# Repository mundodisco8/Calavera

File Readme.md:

# Calavera Badge

We wanted to run a "lunch and learn" day at the company I used to work about soldering. I always liked [Protopic's Day of the Geek Soldering Badge](https://www.proto-pic.co.uk/day-of-the-geek-badge/), but it only turns two LEDs on when you slide the battery, and I thought that my mates would need a bit more than a couple of LEDs to be able to say that they know how to solder, so I thought on modifying. I checked around but it seems the project is not open source, so I decided to ~~blatantly copy~~ get inspired by them.

So here I was, thinking how to improve it, if I should go nuts or keep it simple. Danny, what should I do? should I go simple?

As I wanted to do a bit more, I decided to add two features:

* A way to turn it on and off. I thought adding a slider switch (and that would be a terrific idea in any case). I had never experimented with cap touch, so I thought in giving it a go.
* Add a "breathe" effect to the LEDs.

The schematic includes instructions on pretty much everything, so I recommend checking it. You can choose how challenging you want it to be, from "slide battery to get LEDs on" to "cap touch with breathe effect" and all the possibilities in between.

Turns out the badge is a bit overkill. It took me around 30 minutes to do one, and a colleague that has never soldered took something around 2-3h to finish it.

I was testing Cadlab when I was doing this project, you can view this project [here](https://cadlab.io/project/2044).

## Variants

I wanted to experiment with plated PCB borders. It gives it a very nice touch, but they are expensive, so you might want to make a cheaper version. There are two "footprints" for the soldermask "part", so you can choose to have the plated border or not. You might want to run the "Border" variant even without plated borders to get a nice copper outline, too. In any case, this board is yelling to be finished in ENIG, so please expend some money on that. Is not that expensive.

## The support folder

You can find the original SVG used for the art, as well as some SVGs I used to

## Known Issues / To Do:

* Tweak the cap touch pad / circuitry. Right now the cap touch feature is not very reliable. The values are the standard ones provided in the datasheet. A bit of experimenting could make it more reliable, but who has time for that, right?

## Acknowledgements

* [Terayza](https://github.com/Terayza) for her invaluable help.
* Protopic for doing their Day of the Geek soldering badge. Theirs is infinitely nicer than mine.
* The graphic on the top silkscreen / soldermask is taken from [Freepik](www.freepik.com).
* [The SVG2Shenzhen plugin.](https://github.com/badgeek/svg2shenzhen)
* My mate Danny DV, for being so nice and lending his image for this readme.

## Changelog

### v0.3.1-RC1 - 30th October 2023

* Moved the project to KiCad 7, and took the opportunity to tweak some footprints and the art.
* Made the touch area a bit bigger.

### v0.3.0 (untested, never produced) - 28th October 2022

Slightly improved version.

* Changed the double NMOS for a single one. Package is the "same" than v0.2.0 (SOT23), but having only 3 pins should make it way simpler to solder. We don't drive current, so we don't need two transistors.
* Cleaned the track layout
* Added a switch so you can fully turn it off when not in use.
* Added a couple of good practices from [ST's AN4312](https://www.st.com/resource/en/application_note/dm00087990-design-with-surface-sensors-for-touch-sensing-applications-on-mcus-stmicroelectronics.pdf). Hatched the ground below the pad and made its trace to the sensor thinner. Planes connected to ground which increases the parasitic capacitance on the cap sensor (bad) but it's better than a floating plane as it was before (worse).

### v0.2.0 (untested, never produced) - 10th January 2020

Slightly improved version.

* Cleaned the folder structure. Now all the parts are in the same library, and all the 3D models are relatively referenced to the project path.
* Changed the transistor to a SOT23. Should be easier to solder.
* Increased the track width.
* Made the border slightly thinner, I think? I don't remember. Probably.
* Isolated the ground plane from the copper pour, because I suspect that it will improve the touch response, but I have no idea if it will work.

### v0.1.0 - 23rd September 2019

First version of this board. It works 💃🎉🚀🦼! But not very well 💣🥦...

* Cap touch is hit and miss. I think that the fact that the border is exposed and tied to ground makes that when you hold it, you mess with the electric field. The whole subcircuit might need a makeover.
* The tracks are very thin and can be ripped up by a young padawan.
* The transistor footprint is devilishly difficult to solder even for an experienced Jedi.

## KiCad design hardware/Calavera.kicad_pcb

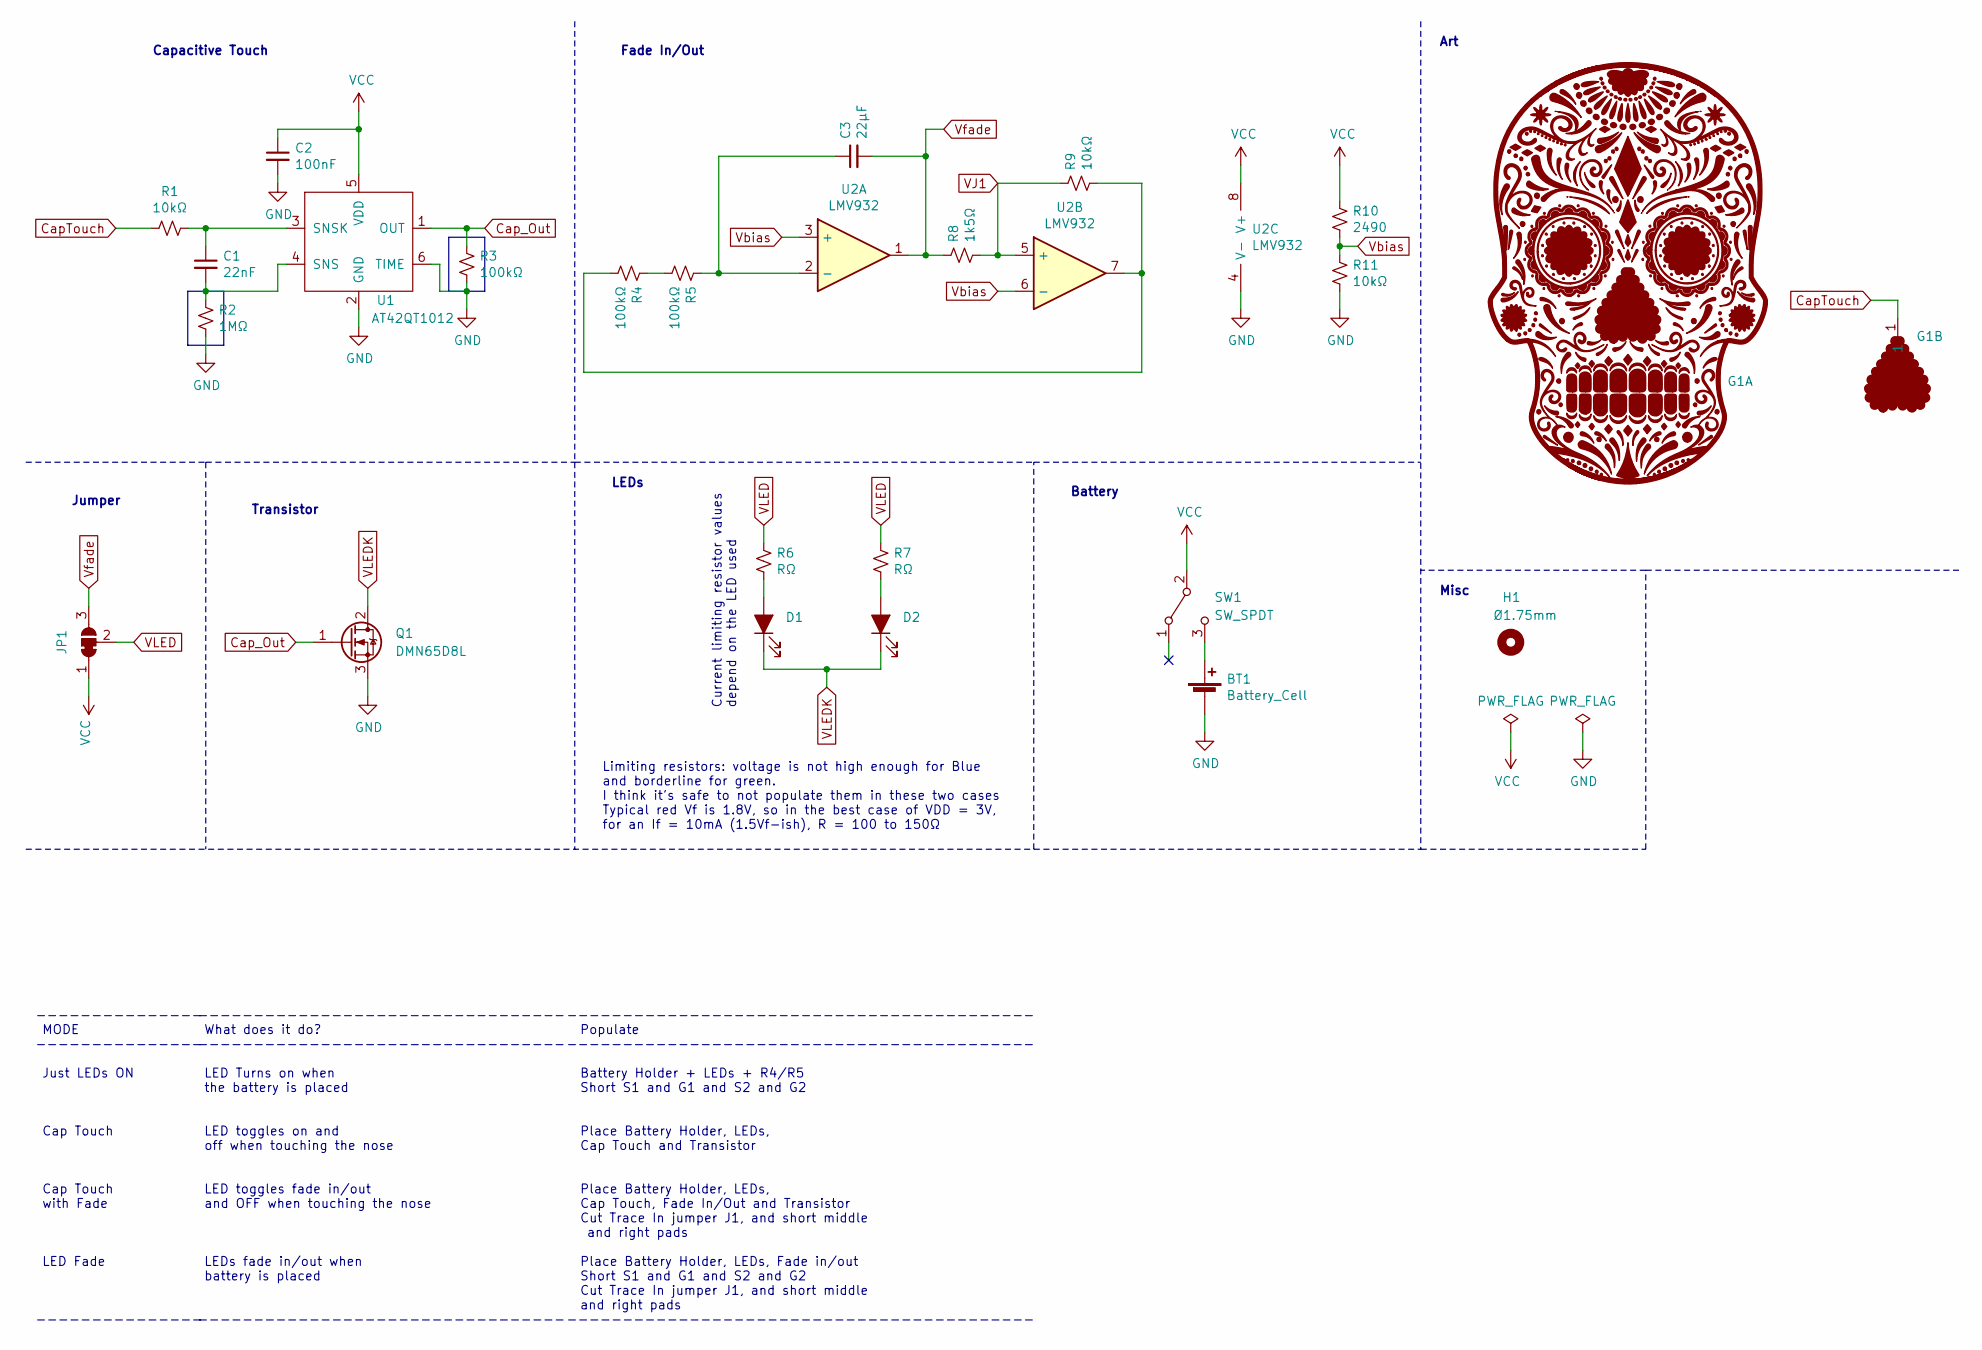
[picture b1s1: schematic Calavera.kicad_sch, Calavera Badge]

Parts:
BT1: Battery_Cell; CR2032_Keystone_3024; MPN 3034; Digikey PN 36-3034-ND
C1: 22nF; 0805-C_Handsolder; Tolerance X7R; MPN 885342207011; Digikey PN 732-12080-1-ND
C2: 100nF; 0805-C_Handsolder; Tolerance X7R; MPN CL21B104KBCNNNC; Digikey PN 1276-1003-1-ND
C3: 22μF; 0805-C_Handsolder; Tolerance X7R; MPN GRM21BZ71A226ME15L; Digikey PN 490-GRM21BZ71A226ME15LCT-ND
D1, D2: LED_Small_ALT; LED_D3.0mm_ThroughHole; MPN N/A; Digikey PN N/A
G1: Calavera_Art; MPN N/A; Digikey PN N/A
H1: Ø1.75mm; MountingHole_1.75mm; MPN N/A; Digikey PN N/A
JP1: SolderJumper_3_Bridged12; SolderJumper-3_P1.3mm_Bridged12_RoundedPad1.0x1.5mm; MPN N/A; Digikey PN N/A
Q1: DMN65D8L; SOT-23_NMOS_DMN65D8L; MPN DMN65D8L; Digikey PN DMN65D8L-7DICT-ND
R1, R9, R11: 10kΩ; 0805-R_Handsolder; Tolerance ±1%, 1/8W; MPN CR0805-FX-1002ELF; Digikey PN CR0805-FX-1002ELFCT-ND
R2: 1MΩ; 0805-R_Handsolder; Tolerance ±1%, 1/8W; MPN CR0805-FX-1004ELF; Digikey PN CR0805-FX-1004ELFCT-ND
R3, R4, R5: 100kΩ; 0805-R_Handsolder; Tolerance ±1%, 1/8W; MPN CR0805-FX-1003ELF; Digikey PN CR0805-FX-1003ELFCT-ND
R6, R7: RΩ; 0805-R_Handsolder; MPN N/A; Digikey PN N/A
R8: 1k5Ω; 0805-R_Handsolder; Tolerance ±1%, 1/8W; MPN CR0805-FX-1501ELF; Digikey PN CR0805-FX-1501ELFCT-ND
R10: 2490; 0805-R_Handsolder; Tolerance ±1%, 1/8W; MPN CR0805-FX-2491ELF; Digikey PN CR0805-FX-2491ELFCT-ND
SW1: SW_SPDT; Slider_Switch_C&K_AYZ0102AGRLC_SPDT_RightAngle; MPN AYZ0102AGRLC; Digikey PN 401-2012-1-ND
U1: AT42QT1012; SOT23-6-AT42QT1012; MPN AT42QT1012-TSHR; Digikey PN 401-2012-1-ND
U2: LMV932; SOIC-8_Dual_OpAmp_Handsolder; MPN LMV932DR2G; Digikey PN LMV932DR2GOSCT-ND

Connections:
CapTouch: G1.1, R1.2
Cap_Out: Q1.1 (G), R3.1, U1.1 (OUT)
GND: BT1.-, C2.2, Q1.3 (S), R2.2, R3.2, R11.2, U1.2 (GND), U1.6 (TIME), U2.4 (V-)
unnamed: D1.2 (A), R6.2
unnamed: D2.2 (A), R7.2
unnamed: R4.1, R5.2
unnamed: R4.2, R9.2, U2.7
unnamed: BT1.+, SW1.3 (C)
unnamed: C1.2, R2.1, U1.4 (SNS)
unnamed: C1.1, R1.1, U1.3 (SNSK)
unnamed: C3.1, R5.1, U2.2 (-)
VCC: C2.1, JP1.1 (A), R10.1, SW1.2 (B), U1.5 (VDD), U2.8 (V+)
VJ1: R8.2, R9.1, U2.5 (+)
VLED: JP1.2 (C), R6.1, R7.1
VLEDK: D1.1 (K), D2.1 (K), Q1.2 (D)
Vbias: R10.2, R11.1, U2.3 (+), U2.6 (-)
Vfade: C3.2, JP1.3 (B), R8.1, U2.1

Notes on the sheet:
Battery
--------------- MODE --------------- Just LEDs ON Cap Touch Cap Touch with Fade LED Fade ---------------
Capacitive Touch
Misc
Current limiting resistor values depend on the LED used
Jumper
Fade In/Out
Transistor
Limiting resistors: voltage is not high enough for Blue and borderline for green. I think it's safe to not populate them in these two cases Typical red Vf is 1.8V, so in the best case of VDD = 3V, for an If = 10mA (1.5Vf-ish), R = 100 to 150Ω
--------------------------------- What does it do? --------------------------------- LED Turns on when the battery is placed LED toggles on and off when touching the nose LED toggles fade in/out and OFF when touching the nose LEDs fade in/out when battery is placed ---------------------------------
------------------------------------------ Populate ------------------------------------------ Battery Holder + LEDs + R4/R5 Short S1 and G1 and S2 and G2 Place Battery Holder, LEDs, Cap Touch and Transistor Place Battery Holder, LEDs, Cap Touch, Fade In/Out and Transistor Cut Trace In jumper J1, a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
LEDs
Art

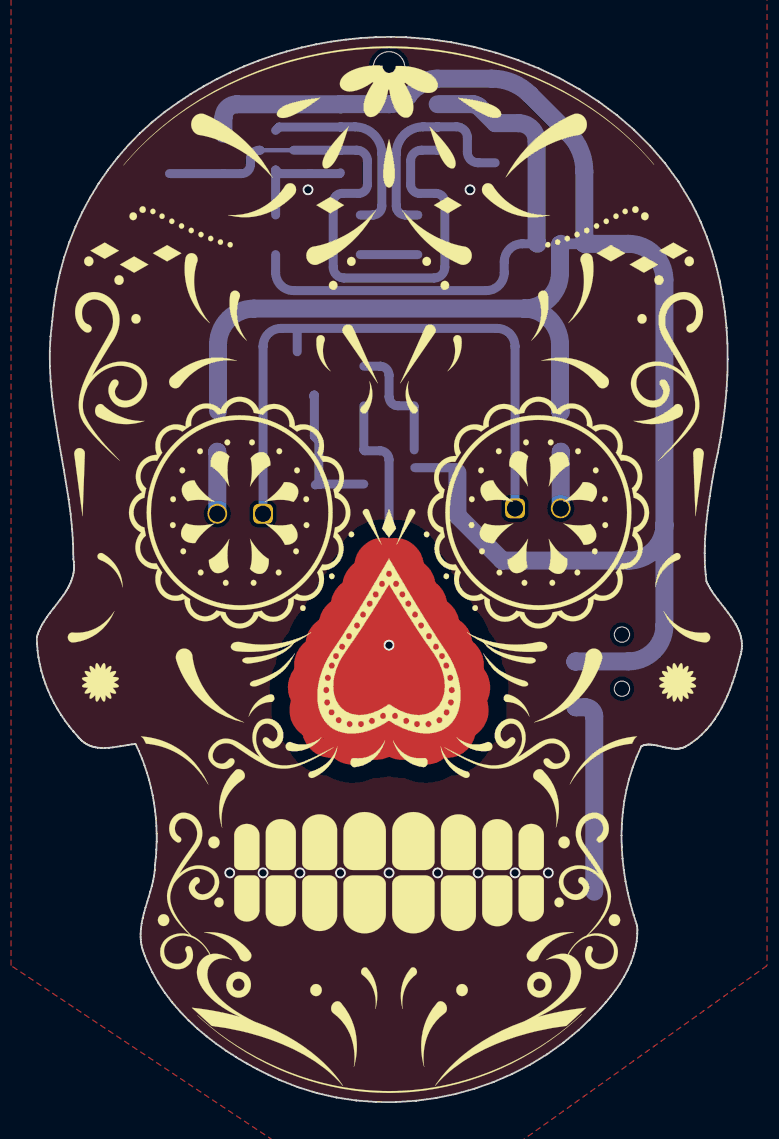
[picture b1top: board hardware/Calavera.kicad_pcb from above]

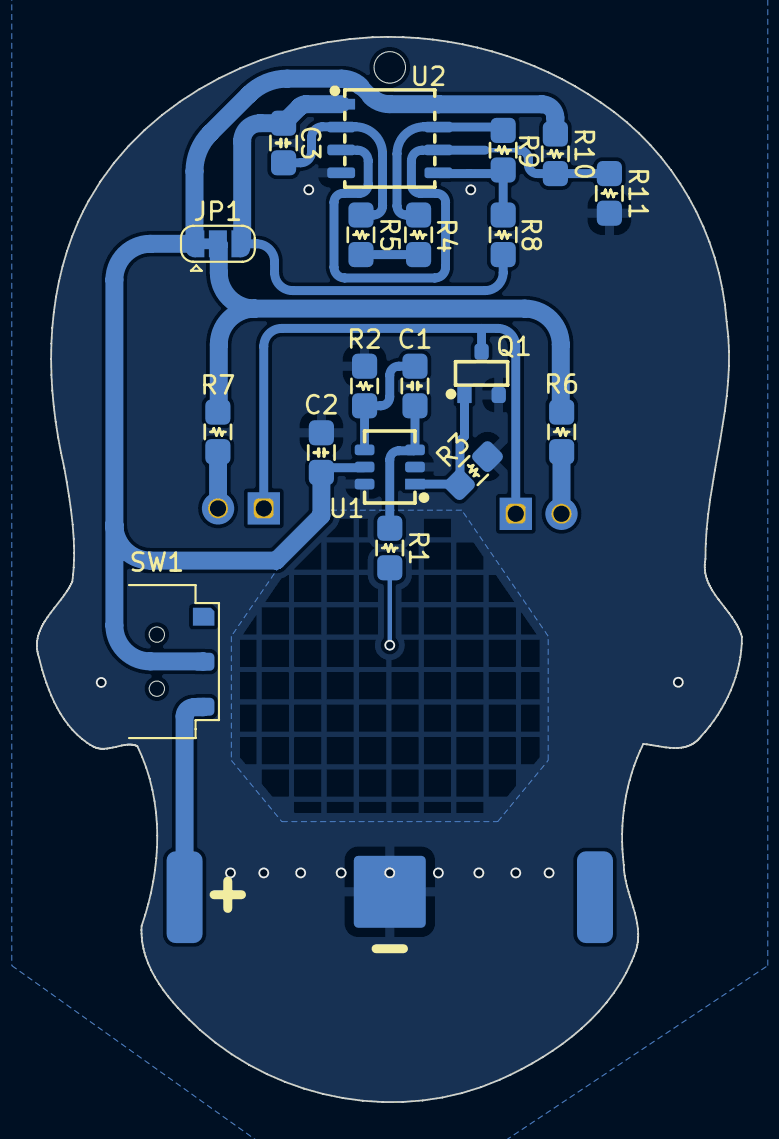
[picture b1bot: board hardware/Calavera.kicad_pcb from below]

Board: 2 copper layers, 39.2 x 59.2 mm, 24 parts (20 on the bottom side), 17 nets.

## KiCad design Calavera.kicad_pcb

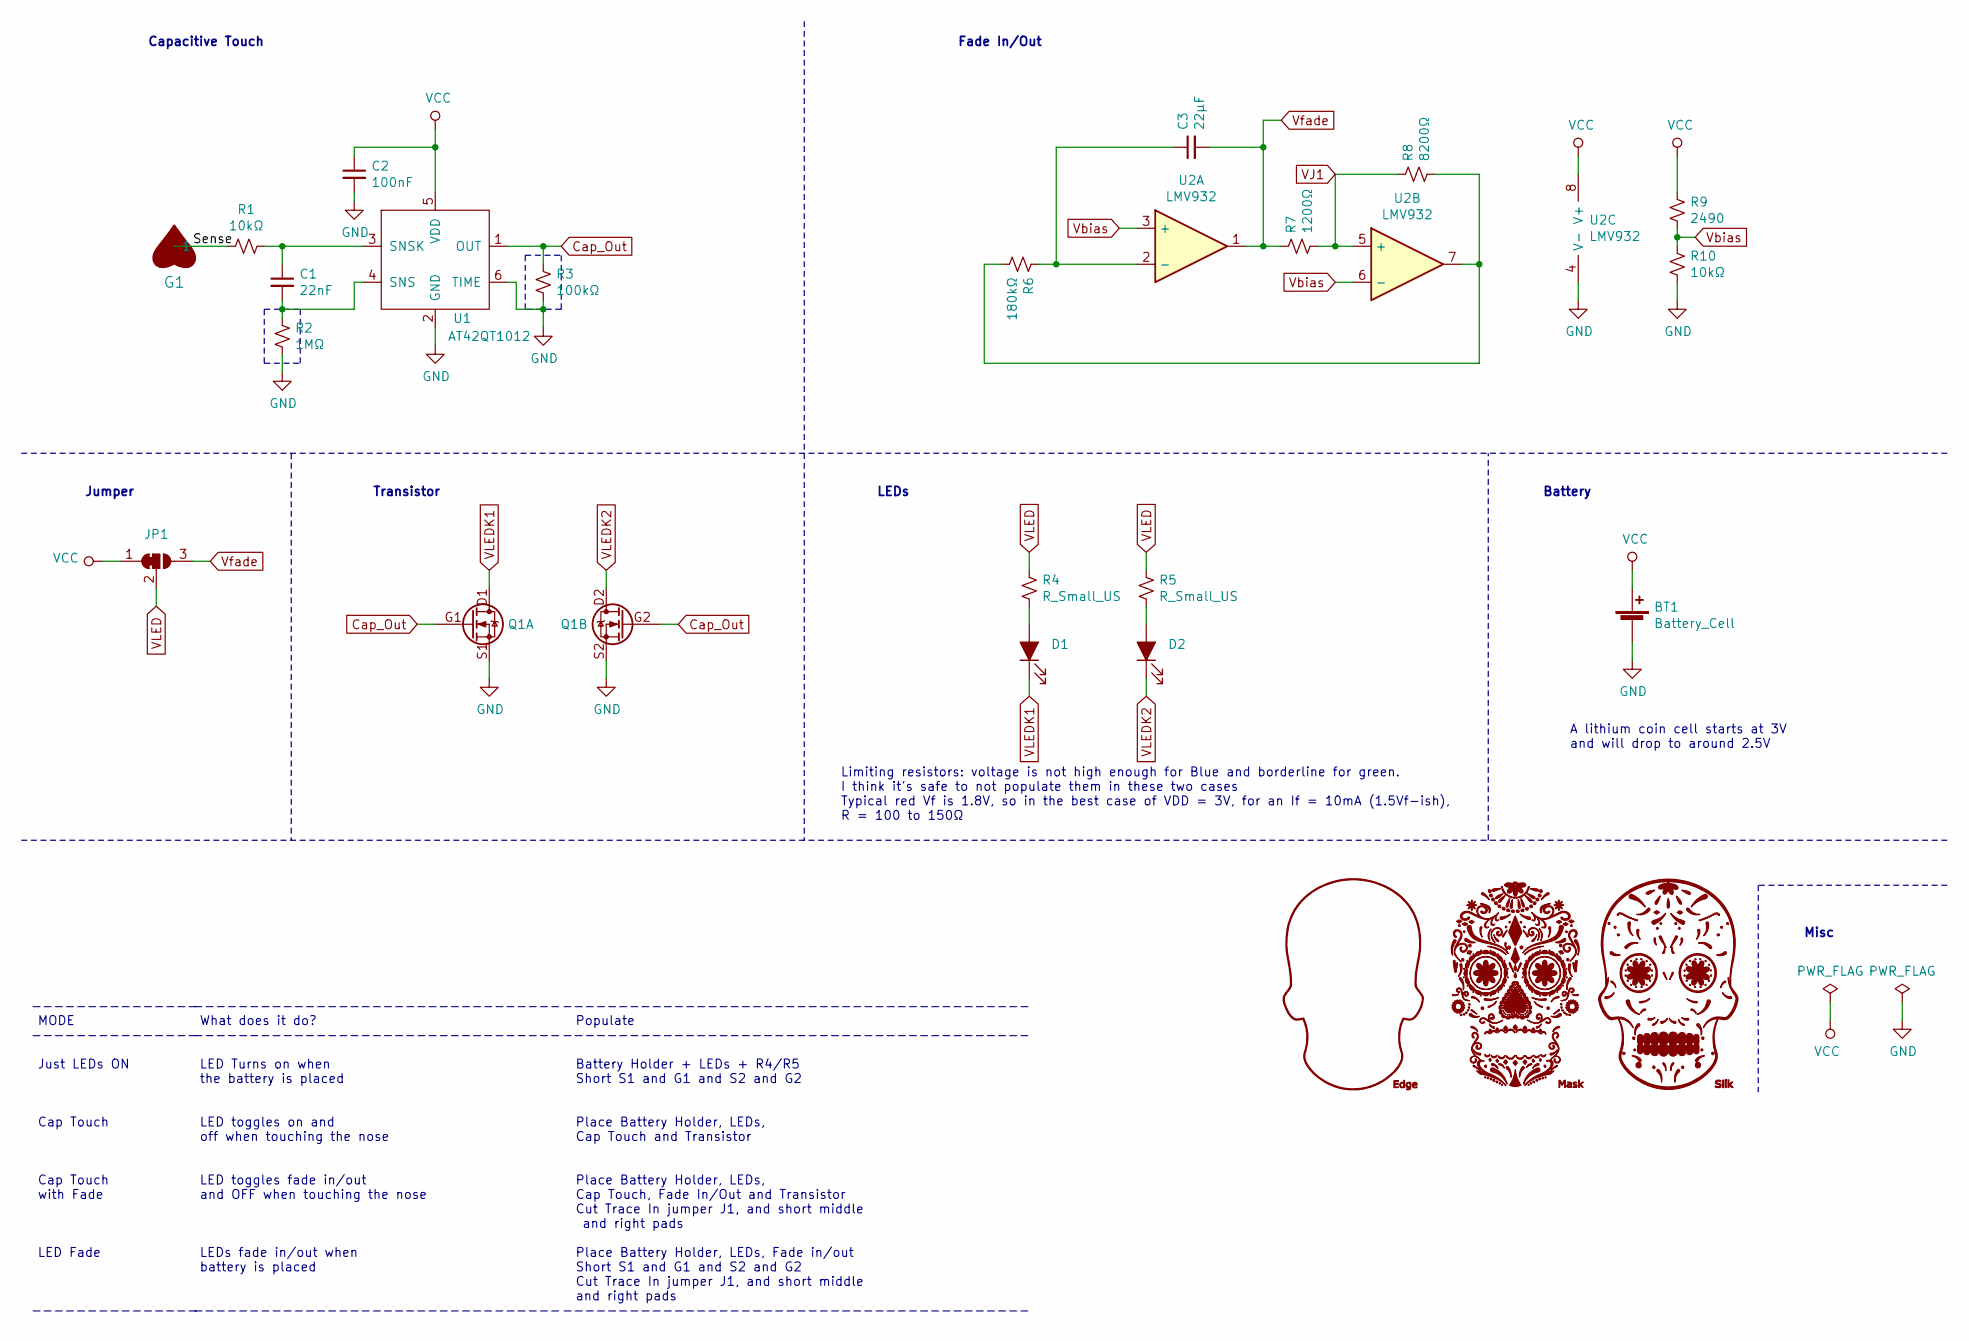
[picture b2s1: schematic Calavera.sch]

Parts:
BT1: Battery_Cell; CR2032_Multicomp_MP000357_Alternative; MPN MP000357
C1: 22nF; 0805-C_Handsolder
C2: 100nF; 0805-C_Handsolder
C3: 22μF; 0805-C_Handsolder
D1, D2: LED_Small_ALT; LED_D3.0mm
G1: HeartPad; Cap_Pad
G2: Edge; Calavera_Board_Margins
G3: Mask; Calavera_SolderMask_1200dpi_Border
G4: Silk; Calavera_SilkScreen_1200dpi
JP1: SolderJumper_3_Bridged12; SolderJumper-3_P1.3mm_Bridged12_RoundedPad1.0x1.5mm
Q1: Q_DUAL_NMOS; SOT23-6-NMOSx2_Handsolder
R1, R10: 10kΩ; 0805-R_Handsolder
R2: 1MΩ; 0805-R_Handsolder
R3: 100kΩ; 0805-R_Handsolder
R4, R5: R_Small_US; 0805-R_Handsolder
R6: 180kΩ; 0805-R_Handsolder
R7: 1200Ω; 0805-R_Handsolder
R8: 8200Ω; 0805-R_Handsolder
R9: 2490; 0805-R_Handsolder
U1: AT42QT1012; SOT23-6-AT42QT1012; MPN AT42QT1012-TSHR
U2: LMV932; SOIC-8_Dual_OpAmp

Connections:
/Sense: G1.1, R1.2
Cap_Out: Q1.G1, Q1.G2, R3.1, U1.1 (OUT)
GND: BT1.-, C2.2, Q1.S1, Q1.S2 (S1), R2.2, R3.2, R10.2, U1.2 (GND), U1.6 (TIME), U2.4 (V-)
unnamed: C1.1, R1.1, U1.3 (SNSK)
unnamed: C1.2, R2.1, U1.4 (SNS)
unnamed: C3.1, R6.1, U2.2 (-)
unnamed: D1.2 (A), R4.2
unnamed: D2.2 (A), R5.2
unnamed: R6.2, R8.2, U2.7
VCC: BT1.+, C2.1, JP1.1 (A), R9.1, U1.5 (VDD), U2.8 (V+)
VJ1: R7.2, R8.1, U2.5 (+)
VLED: JP1.2 (C), R4.1, R5.1
VLEDK1: D1.1 (K), Q1.D1
VLEDK2: D2.1 (K), Q1.D2 (D1)
Vbias: R9.2, R10.1, U2.3 (+), U2.6 (-)
Vfade: C3.2, JP1.3 (B), R7.1, U2.1

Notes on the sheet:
Capacitive Touch
LEDs
Battery
Jumper
Misc
Limiting resistors: voltage is not high enough for Blue and borderline for green. I think it's safe to not populate them in these two cases Typical red Vf is 1.8V, so in the best case of VDD = 3V, for an If = 10mA (1.5Vf-ish), R = 100 to 150Ω
A lithium coin cell starts at 3V and will drop to around 2.5V
--------------- MODE --------------- Just LEDs ON Cap Touch Cap Touch with Fade LED Fade ---------------
--------------------------------- What does it do? --------------------------------- LED Turns on when the battery is placed LED toggles on and off when touching the nose LED toggles fade in/out and OFF when touching the nose LEDs fade in/out when battery is placed ---------------------------------
------------------------------------------ Populate ------------------------------------------ Battery Holder + LEDs + R4/R5 Short S1 and G1 and S2 and G2 Place Battery Holder, LEDs, Cap Touch and Transistor Place Battery Holder, LEDs, Cap Touch, Fade In/Out and Transistor Cut Trace In jumper J1, a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
Fade In/Out
Transistor

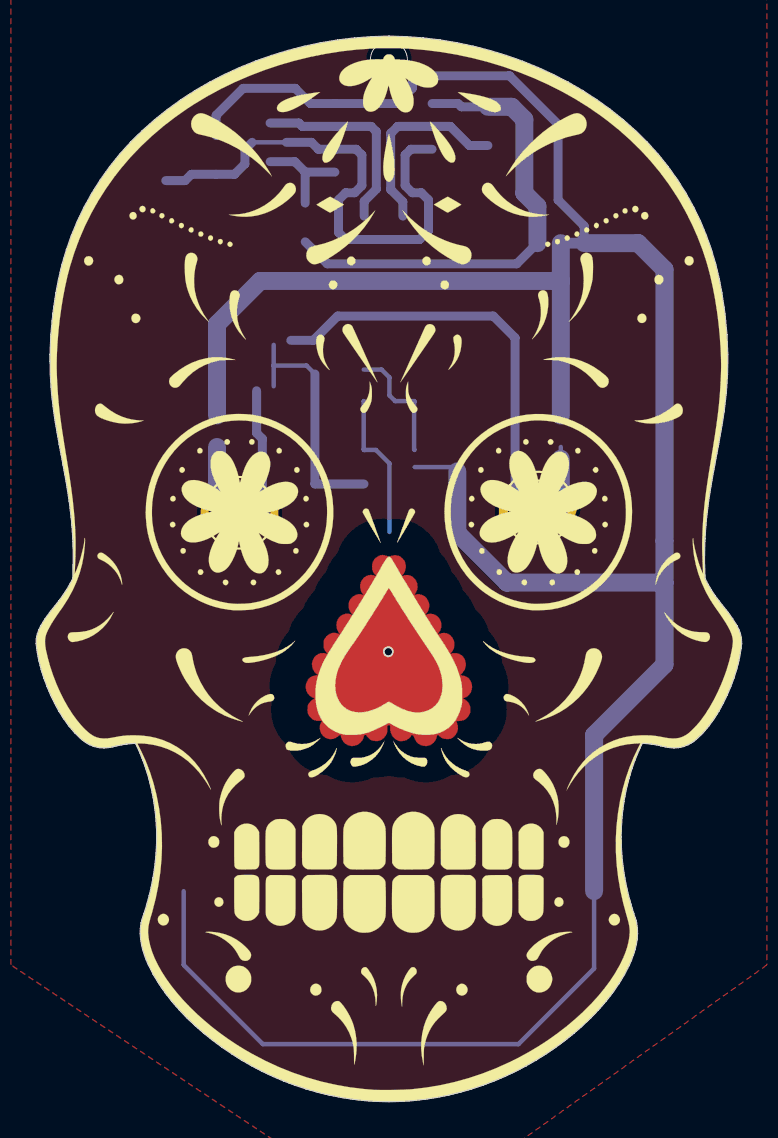
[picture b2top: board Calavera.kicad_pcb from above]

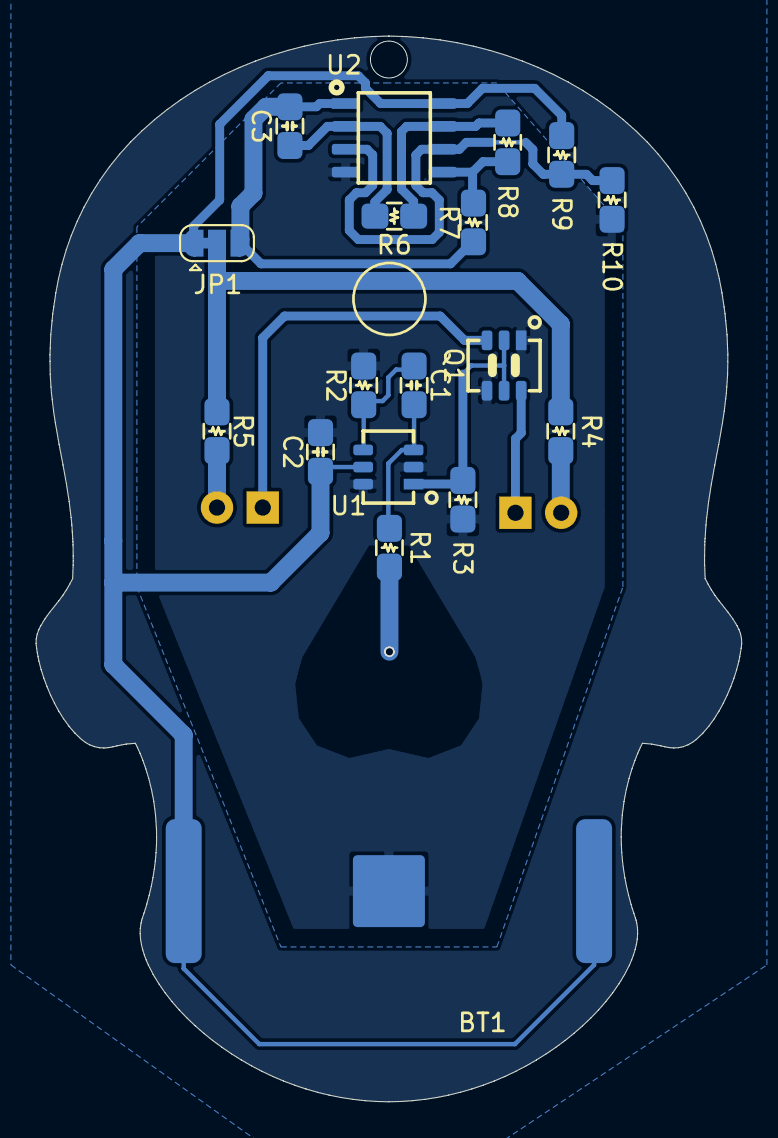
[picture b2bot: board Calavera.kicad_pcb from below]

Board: 2 copper layers, 39.2 x 59.2 mm, 24 parts (18 on the bottom side), 16 nets.

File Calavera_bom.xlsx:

Description | Part | References | Value | Footprint | Quantity Per PCB | Total Qty | Datasheet | MPN | Farnell (@50) | RS (@50) | digikey (@50) | Digikey PN | Ebay | Column1
Battery Cell Holder |  | BT1 | Battery_Cell |  | 1 | 50 | http://www.farnell.com/datasheets/2820927.pdf | 3034 | 0.51 | 0.65 | 0.19 | 36-3034-ND |  | Digikey Alternative: Keystone 3034
Capacitor |  | C2 | 100nF | 0805 | 1 | 50 |  | CL21B104MBCNNNC |  |  | 2.8000000000000001E-2 | 1276-2450-1-ND
Capacitor |  | C1 | 22nF | 0805 | 1 | 50 |  | 885012207068 |  |  | 0.03 | ‎732-8057-1-ND‎
Capacitor |  | C3 | 22μF | 0805 | 1 | 50 |  | CL21A226MOCLRNC |  |  | 5.6000000000000001E-2 | ‎1276-6780-1-ND‎
 |  |  | 47μF | 0805 | 1 | 50 |  | CL21A476MQYNNNE |  |  | 9.7000000000000003E-2 | ‎1276-1852-1-ND‎ |  | Just in case, get 20?
LED |  | D1 D2 |  | LED_D3.0mm | 2 | 100 |  |  |  |  |  |  | 0.15 | £3.14 for 50, £2.14 for 20
Dual NMOS | NX138BKS | Q1 |  | SOT-363 | 1 | 50 | https://assets.nexperia.com/documents/data-sheet/NX138BKS.pdf | NX138BKSX | N/A | N/A | 0.2 | 1727-2733-1-ND‎
Resistor |  | R3 | 100kΩ | 0805 | 1 | 50 |  | RMCF0805FT100K |  |  | 2.1999999999999999E-2 | RMCF0805FT100KCT-ND
Resistor |  | R1 R10 | 10kΩ | 0805 | 2 | 100 |  | RMCF0805FT10K0 |  |  | 2.1999999999999999E-2 | RMCF0805FT10K0CT-ND
Resistor |  | R7 | 1200Ω | 0805 | 1 | 50 |  | RMCF0805FT1K20 |  |  | 2.1999999999999999E-2 | RMCF0805FT1K20CT-ND
Resistor |  | R6 | 180kΩ | 0805 | 1 | 50 |  | RMCF0805FT180K |  |  | 2.1999999999999999E-2 | RMCF0805FT180KCT-ND
Resistor |  | R2 | 1MΩ | 0805 | 1 | 50 |  | RMCF0805FT1M00 |  |  | 2.1999999999999999E-2 | RMCF0805FT1M00CT-ND
Resistor |  | R9 | 2490Ω | 0805 | 1 | 50 |  | RMCF0805FT2K49 |  |  | 2.1999999999999999E-2 | RMCF0805FT2K49CT-ND
Resistor |  | R8 | 8200Ω | 0805 | 1 | 50 |  | RMCF0805FT8K20 |  |  | 2.1999999999999999E-2 | RMCF0805FT8K20CT-ND
Resistor |  | R4 R5 | 100Ω | 0805 | 2 | 100 |  | RMCF0805FT100R |  |  | 2.1999999999999999E-2 | RMCF0805FT100RCT-ND |  | 10mA @Vbat=3V
Cap Touch Sensor | AT42QT1012 | U1 |  | SOT23-6 | 1 | 50 | http://ww1.microchip.com/downloads/en/devicedoc/40001948a.pdf | AT42QT1012-TSHR | 0.43 | 0.47 | 0.45 | AT42QT1012-TSHRCT-ND‎
Dual Opamp | LMV932 | U2 |  | SOIC-8 | 1 | 50 | https://www.onsemi.com/pub/Collateral/LMV931-D.PDF | LMV932DR2G | 0.34 | 0.1 | 0.36 | LMV932DR2GOSCT-ND‎
Battery Cell |  | CR2032 |  | CR2032 | 1 | 50 |  |  |  |  |  |  | 0.14349999999999999 | Branded ones!
Pin Tacks |  |  |  |  | 1 | 50 |  |  |  |  |  |  | 8.8000000000000009E-2 | https://www.ebay.co.uk/itm/TIE-TAC-TACK-PIN-FLAT-PAD-TIE-SQU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
 |  |  |  |  |  |  |  | Non-pasives | 1.28 | 1.22 | 1
 |  |  |  |  |  |  |  | TOTAL | 90.575000000000003 | 87.575000000000003 | 87.575000000000003
 |  |  |  |  |  |  |  | PER BOARD | 1.8115000000000001 | 1.7515000000000001 | 1.7515000000000001

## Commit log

2019-08-19 Started the repo
2019-08-19 First commit of project files. The project is ready for manufacture, but there's still some cleaning to do
2019-08-20 Added Silk, Mask and Edge as schematic symbols Updated silk and mask, as they got misaligned Added silk to the nose pad
2019-08-20 Backlink to CADLAB.io has been added.
2019-08-22 Added an exposed outline around the board (and extended the copper plane to the PCB edge) to try to get the side plated too. Changed the Silk and Soldermask parts for this change, and also corrected 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
2019-08-23 Tweaked a couple of things on the PCB as the exposed copper on the edge of the PCB could make soldering a tad difficult
2019-08-23 Removed border plating and exposed border Sadly, it increased the cost x3!
2019-09-23 v1.0 - Manufactured for the lunch and learn
2019-09-23 Better assembly drawings
2019-10-04 Kiplot config
2019-10-07 4 Layer test
2019-10-08 added layer in2
2019-10-08 no message
2019-10-17 Modified three library parts
2019-10-17 First stab at an orb
2019-10-18 Added BoM xml
2020-01-09 Made tracks thicker, as they are easier to rip when overheat than I thought they would be
2020-01-09 Removed the Jumpers as they are not needed
2020-01-10 Changed the transistor footprint to a SOT23 as it was very tricky to solder.
2020-01-10 Put everything on a single library, and the 3D models are now relative to the project path
2020-01-10 Cleaning here and there
2020-01-10 Simple inline orb that does gerbers and positions
2020-01-10 Change setup to use the orb
2020-01-13 Bumped orb version to fix an issue with gerbers not being generated
2020-01-14 Generate BoM
2020-01-14 Create LICENSE
2020-01-14 Bumped Orb version
2020-01-14 Added render to readmen
2020-01-14 Support, not support
2022-10-27 Updated To KiCad6
2022-10-28 v0.3.0 see changelog for details
2023-01-17 Cap touch area is bigger. Added some vias to connect both planes
2023-01-18 Added KiBot as CICD and removed CircleCI Fixed some DRC/ERC errors and tweaked the files so KiBot accepts them and generates artifacts from them
2023-01-18 Uncomment all the actions on KiBot
2023-01-18 Adding verbose output
2023-01-18 Changed the output dir in Github
2023-01-18 Final tweak, gerbers are uploaded as a separate file
2023-01-18 did I say final tweak?
2023-02-10 Trigger Github Actions on library file modification too!
2023-10-27 Small edit of the Art. Small changes here and there to account for new DRCs in KiCad 7
2023-10-27 Hand tweaks to the art to avoid most of the ERC errors
2023-10-30 Tweaks on the project for KiBot
2023-10-30 CICD-ing
2023-10-30 CICD 2
2023-10-30 CICD3
2023-10-30 diagnose permission denied in CICD
2023-10-30 fix permissions issue on CICD
2023-10-30 Continuous Integration Build Artifacts
2023-10-30 fixed actions
2023-10-31 Put some sense and changed resistor values to reduce the number of individual parts Removed ignored files and renamed a folder
2023-10-31 Simplified the values of the resistors * Added a new resistor * Moved tracks around * Added two vias to get GND to the bottom copper in an isolated island * Cleaned fabrication
2023-11-01 More Fab cleaning
2023-11-03 3D model behaves again
